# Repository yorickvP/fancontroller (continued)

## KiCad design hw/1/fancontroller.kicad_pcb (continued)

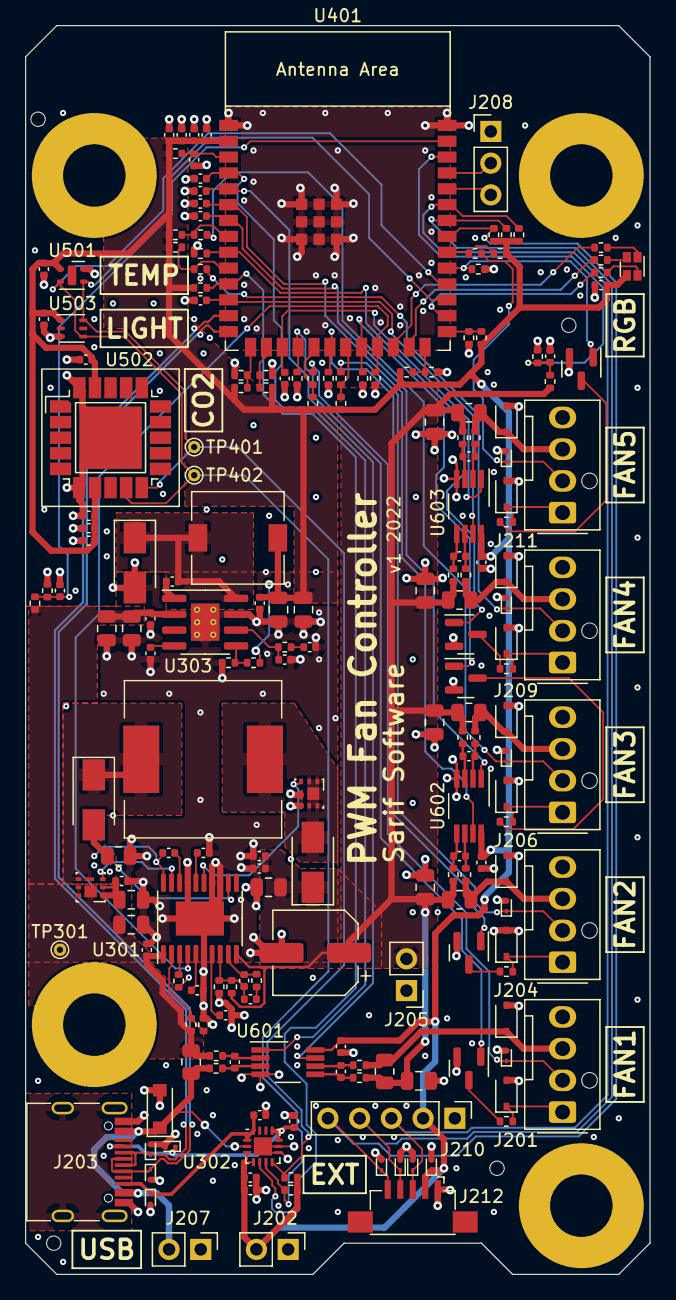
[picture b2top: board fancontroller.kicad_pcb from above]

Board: 4 copper layers, 50.0 x 100.0 mm, 203 parts (0 on the bottom side), 99 nets.

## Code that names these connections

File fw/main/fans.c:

#include "fans.h"

#include <driver/ledc.h>
#include <freertos/FreeRTOS.h>
#include <freertos/semphr.h>
#include <string.h>

#include "led.h"
#include "util.h"

#define TAG "fans"

#define LEDC_TIMER LEDC_TIMER_0
#define LEDC_MODE LEDC_LOW_SPEED_MODE
#define LEDC_DUTY_RES LEDC_TIMER_8_BIT
#define LEDC_FREQUENCY (24000)

#define LEDC_FAN1_CHANNEL (LEDC_CHANNEL_0)
#define LEDC_FAN2_CHANNEL (LEDC_CHANNEL_1)
#define LEDC_FAN3_CHANNEL (LEDC_CHANNEL_2)
#define LEDC_FAN4_CHANNEL (LEDC_CHANNEL_3)
#define LEDC_FAN5_CHANNEL (LEDC_CHANNEL_4)

#define GPIO_FAN1_PWM (10)
#define GPIO_FAN2_PWM (12)
#define GPIO_FAN3_PWM (14)
#define GPIO_FAN4_PWM (16)
#define GPIO_FAN5_PWM (38)
#define GPIO_12V_EN (21)

static fans_pwm8_t s_state;
static SemaphoreHandle_t s_mutex;

static esp_err_t channel_config(ledc_channel_t channel, int gpio_num)
{
    ledc_channel_config_t config = {
        .speed_mode = LEDC_MODE,
        .channel = channel,
        .timer_sel = LEDC_TIMER,
        .intr_type = LEDC_INTR_DISABLE,
        .gpio_num = gpio_num,
        .duty = 0xff, // Set duty to 100% (inverted)
        .hpoint = 0
    };
    return ledc_channel_config(&config);
}

static bool fans_persist_channel_unsafe(ledc_channel_t channel, fan_pwm8_t duty)
{
    if (duty == 0x00) {
        ESP_ERROR_CHECK(ledc_stop(LEDC_MODE, channel, 1)); // Inverted
    } else {
        ESP_ERROR_CHECK(ledc_set_duty(LEDC_MODE, channel, 0xff - duty)); // Inverted
        ESP_ERROR_CHECK(ledc_update_duty(LEDC_MODE, channel));
    }
    return duty > 0;
}

static void fans_persist_unsafe(void)
{
    bool any = false;

    any |= fans_persist_channel_unsafe(LEDC_FAN1_CHANNEL, s_state[0]);
    any |= fans_persist_channel_unsafe(LEDC_FAN2_CHANNEL, s_state[1]);
    any |= fans_persist_channel_unsafe(LEDC_FAN3_CHANNEL, s_state[2]);
    any |= fans_persist_channel_unsafe(LEDC_FAN4_CHANNEL, s_state[3]);
    any |= fans_persist_channel_unsafe(LEDC_FAN5_CHANNEL, s_state[4]);

    gpio_set_level(GPIO_12V_EN, any);

    // TODO Temporary emotes until controller is written
    if (any) {
        led_set_color((rgb_t) {
            .r = 0x00,
            .g = 0x10,
            .b = 0x00,
        });
    } else {
        led_set_color((rgb_t) {
            .r = 0x10,
            .g = 0x00,
            .b = 0x00,
        });
    }
}

esp_err_t fans_init(void)
{
    s_mutex = xSemaphoreCreateMutex();

    gpio_config_t io_conf = {
        .intr_type = GPIO_INTR_DISABLE,
        .mode = GPIO_MODE_OUTPUT,
        .pin_bit_mask = (1ULL << GPIO_12V_EN),
        .pull_down_en = 0,
        .pull_up_en = 0,
    };
    gpio_config(&io_conf);

    ledc_timer_config_t ledc_timer = {
        .speed_mode = LEDC_MODE,
        .timer_num = LEDC_TIMER,
        .duty_resolution = LEDC_DUTY_RES,
        .freq_hz = LEDC_FREQUENCY,
        .clk_cfg = LEDC_AUTO_CLK
    };
    ESP_ERROR_CHECK(ledc_timer_config(&ledc_timer));

    ESP_ERROR_CHECK(channel_config(LEDC_FAN1_CHANNEL, GPIO_FAN1_PWM));
    ESP_ERROR_CHECK(channel_config(LEDC_FAN2_CHANNEL, GPIO_FAN2_PWM));
    ESP_ERROR_CHECK(channel_config(LEDC_FAN3_CHANNEL, GPIO_FAN3_PWM));
    ESP_ERROR_CHECK(channel_config(LEDC_FAN4_CHANNEL, GPIO_FAN4_PWM));
    ESP_ERROR_CHECK(channel_config(LEDC_FAN5_CHANNEL, GPIO_FAN5_PWM));

    fans_persist_unsafe();

    return ESP_OK;
}

esp_err_t fans_command(uint8_t fan_i, fan_pwm8_t duty)
{
    if (fan_i > ARRAY_SIZE(s_state)) {
        return ESP_ERR_INVALID_ARG;
    }

    xSemaphoreTake(s_mutex, portMAX_DELAY);
    s_state[fan_i] = duty;
    fans_persist_unsafe();
    xSemaphoreGive(s_mutex);

    return ESP_OK;
}

esp_err_t fans_fetch(fans_pwm8_t duty_out)
{
    xSemaphoreTake(s_mutex, portMAX_DELAY);
    memcpy(duty_out, s_state, sizeof(s_state));
    xSemaphoreGive(s_mutex);

    return ESP_OK;
}

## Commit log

2023-11-10 Added revision 1 of hw
2023-11-10 Added rudimentary i2c bus locking
2023-11-11 Added default sdkconfig
2023-11-13 Support newest ESP_IDF, added channels for temperature
2023-11-14 Revert data back to ESP-IDF v5.1.1
2023-11-14 Added note about which ESP-IDF we use
2023-11-14 Removed MQTT5 specific code to make it version agnostic
2023-11-14 Added MQTT broker URL to KConfig
2023-11-14 Only report when connected to MQTT, and only have the MQTT service running when eth is up
2023-11-14 Ran clang-format
2023-11-14 Added .vscode to .gitignore
2023-11-14 Added rudimentary LED emotes
2023-11-14 Check for presence of external temperature sensor
2023-11-14 Do not emit empty object block if temperature measurement is invalid
2023-11-14 Updated FW readme with TODO's
2023-11-15 Disable LEDC channel if duty cycle is 0
2023-11-18 Add esp-idf v4.4.3
2023-11-18 esp-idf: 4.4.3 -> 5.1.2
2023-11-18 Add fw derivation
2023-11-18 esp-idf: 5.1.2 -> 5.1.1
2023-11-18 working fw build
2023-11-18 Add github actions
2023-11-18 Clean up flake.nix
2023-11-18 render schemas and gerbers in CI
2023-11-19 Tweak output names
2023-11-19 Add 3d rendering output
2023-11-19 tacho: replace by pcnt peripheral
2023-11-23 Add some OTA code
2023-11-23 Add shell with clangd
